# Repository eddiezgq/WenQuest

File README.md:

# 问渠 WenQuest v0.2

问渠 WenQuest：自研前端（网页 + 微信小程序，一套 uni-app 代码）+ 接口网关（FastAPI）+ 开源教学引擎 Moodle 5.2（Claude / DeepSeek 模型接入）。一条命令启动。

v0.3 新增：**AI 建课**。老师描述课程主题、学习对象和章节数（可粘贴自己的大纲或讲义），AI 先出课程大纲，老师修改确认后 AI 逐课撰写内容，预览无误一键发布成真实课程（章节、阅读页、作业），支持中文、英文或中英双语。

v0.2：问渠自己的学习界面和接口网关。学生登录后可看我的课程、课程目录、阅读页、链接、作业说明和文件，中英文一键切换；新界面暂未支持的活动一键跳到经典界面。下一步：带出处的课程 AI 助教。

## 包里有什么

| 内容 | 说明 |
| --- | --- |
| `apps/web/` | 问渠前端（uni-app + Vue 3）：`npm run dev:h5` 本地开发，`npm run build:mp-weixin` 出微信小程序 |
| `services/gateway/` | 接口网关（FastAPI）：登录、课程、内容、文件代理、中英文解析；`python -m pytest` 运行测试 |
| `moodle/setup_wenquest.php` | 启动时开启网关所需的 Web 服务和多语言过滤器 |
| `plugins/local_wenquest/` | 自研 Moodle 插件：一次调用创建整门课程（AI 建课用），并告诉网关当前用户能否建课 |
| `plugins/aiprovider_claude/` | 自研 Moodle 插件：把 Anthropic Claude 接入 Moodle AI 子系统 |
| `moodle/Dockerfile` | Moodle 5.2 镜像（PHP 8.3 + Apache），已内置 Claude 插件和中文语言包 |
| `docker-compose.yml` | Moodle、PostgreSQL 16、Redis、定时任务四个服务 |
| `moodle/setup_ai.php` | 启动时按 `.env` 自动配置 AI 模型、启用 AI 功能、设置中文和时区 |
| `.env.example` | 配置模板 |
| `docker-compose.prod.yml`、`deploy/` | 云服务器生产部署：Caddy 自动 HTTPS、更新、回滚、备份与恢复脚本 |
| `.github/workflows/deploy.yml` | 推送即自动构建镜像并部署到服务器 |
| `site/` | 学院官网（静态页面，中英双语） |
| `factory/` | 问渠数字工厂：ERPNext 减速器厂（`factory/`）与数字工厂第 1 轮（`factory/digital/`：统一数据总线、仿真车间、看板、AI 工厂助手、Node-RED 桥接、FreeCAD 发布）；单独用 Docker 运行，见 `factory/digital/README.md`。只改这里不会触发服务器部署 |
| `docs/上线手册.md` | 从零上线到 DigitalOcean 的分步手册 |

启用后，Moodle 里立即可用的 AI 功能：

- **课程助手**：学生和教师在课程页面一键“总结本页”“解释这段内容”。
- **编辑器 AI**：在任何富文本编辑器里让 AI 起草文字（教案、作业说明、公告等）。

## 上线到云服务器

按 [docs/上线手册.md](docs/上线手册.md) 操作：官网在主域名，问渠学习平台在 `learn.` 子域名，经典界面（Moodle）在 `classic.` 子域名，推送代码即自动部署，每天自动备份。

## 本地快速试用

需要一台 Linux 服务器（建议 4 核 8 GB 内存以上）并安装 Docker 24+。

```bash
cp .env.example .env
nano .env                      # 至少填：MOODLE_WWWROOT、两个密码、一个 AI 密钥
docker compose up -d --build   # 首次构建约 10–20 分钟
docker compose logs -f moodle  # 看到 "Created AI provider" 即完成
```

浏览器打开 `MOODLE_WWWROOT`（经典界面），用 `.env` 里的管理员账号登录、建课、加学生；再打开 `APP_URL`（默认 http://localhost:8088）用学生账号登录问渠新界面。

## AI 建课

- 需要在 `.env` 里填 `ANTHROPIC_API_KEY`（或国内部署填 `DEEPSEEK_API_KEY`），改完执行 `deploy/update.sh`。
- 管理员自动有建课权限。给老师开权限：经典界面 → 网站管理 → 用户 → 权限 → 分配系统角色 → **课程创建者**，把老师加进去。老师重新登录问渠后，“我的课程”右上角会出现 **AI 建课** 按钮。
- AI 生成的内容只是初稿，发布前请老师逐课预览；发布后也可以在经典界面里继续修改。

### 上传资料建课（v0.4）

老师把整个课程资料文件夹拖进来（或点“选择文件夹”），问渠会：

1. 读取 PDF、Word、PPT（含备注）、Excel、文本和图片（单个文件 ≤ 50 MB，一次最多 300 个）；
2. 按文件名、所在文件夹和内容自动分类：教学大纲、教学日历、教案、讲义、课件、作业、测验、参考答案、实验、评分标准、素材；识别每个文件属于第几章，拿不准的标“请确认”，再交给 AI 补判（AI 不会改老师改过的分类）；
3. 老师核对表格后，按资料生成大纲：每章一节，讲义里的小节标题（如 1.1、1.2）变成课，作业文件变成作业，另有“课程说明”“实验”“测验与复习”；
4. AI 撰写每一课时以本章讲义、教案、课件为依据，并注明出处（如“参考：讲义 第 3 页”）；
5. 发布时原始文件作为附件放进对应章节。**教案和参考答案自动设为学生不可见**，只有老师能看到。

扫描版 PDF（图片）暂时读不出文字，会标“无法读取”，仍可作为附件上传。上传的资料只在服务器临时目录保留 24 小时。

## 模型选择

| 场景 | 设置 |
| --- | --- |
| 在美国开发、演示 | 填 `ANTHROPIC_API_KEY`（在 console.anthropic.com 申请；claude.ai 订阅不含 API） |
| 中国大陆部署 | 填 `DEEPSEEK_API_KEY`。DeepSeek 已完成生成式 AI 服务备案，Moodle 5.2 已内置其插件 |
| 两个都填 | 两个模型都启用，在“网站管理 → AI → AI 提供方”里调整优先顺序 |

可选 Claude 模型：`claude-sonnet-5`（默认，质量与速度均衡）、`claude-opus-5-5`（最强，适合复杂批改）、`claude-haiku-4-5-20251001`（最快、成本最低）。
改 `.env` 后执行 `docker compose up -d`，重启时自动更新配置。

## 在中国大陆部署的注意事项

- **合规**：Anthropic 不对中国大陆提供服务；面向国内学校提供生成式 AI 服务须使用已备案模型，并在属地网信办登记。国内部署请只填 `DEEPSEEK_API_KEY`。
- **网络**：Docker Hub 和 GitHub 在国内可能很慢或无法访问。
  - 给 Docker 配置国内镜像加速器（阿里云、腾讯云控制台均提供）。
  - 构建时换成可访问的 Moodle 仓库镜像：
    `docker compose build --build-arg MOODLE_GIT=<镜像地址>`
- **HTTPS**：`docker-compose.prod.yml` 里的 Caddy 会自动申请证书；也可以改用 Nginx 或云负载均衡，并设 `MOODLE_SSLPROXY=true`。

## 只安装插件（已有 Moodle 5.1 及以上）

用 `aiprovider_claude.zip`（GitHub Actions 每次构建都会生成，在该次运行的 Artifacts 里下载）：网站管理 → 插件 → 安装插件 → 上传 zip。
然后在“网站管理 → AI → AI 提供方”新建 Claude 实例并填入 API 密钥，再到“AI 调用位置”启用课程助手和编辑器。

## 日常运维

生产服务器上用 `deploy/` 里的脚本（见上线手册“日常维护”）。本地试用时：

```bash
docker compose ps                                   # 查看状态
docker compose exec db pg_dump -U moodle moodle > backup.sql   # 备份数据库
docker compose up -d --build                        # 更新插件或 Moodle 后重新构建，自动升级数据库
```

`moodledata`（上传的文件）和 `dbdata`（数据库）存放在 Docker 卷中，重建容器不会丢失，但请定期备份。

## 测试情况（v0.1）

- 插件单元测试 23 项全部通过（Moodle 5.2.3，PHP 8.4，PostgreSQL 16）。
- 端到端：通过 Moodle AI 管理器调用生成、摘要、解释三种动作均成功；对真实 Anthropic API 的请求格式和认证已验证（用无效密钥得到预期的 401）。
- 安装流程（生成配置 → 安装数据库 → 配置 AI → 升级）已在全新数据库上验证。
- Docker 镜像本身尚未在服务器上实际构建过，首次构建如有报错请把日志发回。

## 许可

插件与部署脚本以 GNU GPL v3 或更高版本发布，与 Moodle 一致。

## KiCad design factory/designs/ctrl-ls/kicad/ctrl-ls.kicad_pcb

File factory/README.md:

# 问渠虚拟工厂（ERPNext 版）

一座只生产一种产品的虚拟工厂：**二级圆柱齿轮减速器 WQR-105**（传动比 10.5）。装好后，ERPNext 里已经有完整的产品结构、工艺路线、工作中心、质量检验方案、供应商和客户，学生可以直接从销售订单做到发货，走通 MRP、采购、车间报工、质检、序列号追溯和成本核算。

| 文件 | 内容 |
| --- | --- |
| `docker-compose.yml` | ERPNext v16.34.1 单机版（基于官方 frappe_docker），浏览器端口 8090 |
| `seed.py` | 一键导入工厂主数据（可重复运行） |
| `factory/data.py` | 工厂的全部数据：物料、BOM、工艺、工位、检验标准。改工厂就改这个文件 |
| `工厂设计.md` | 工厂设计说明：传动设计、产品结构、成本、瓶颈分析（由 data.py 自动生成） |
| `实验指导.md` | 6 个教学实验：从接单到发货，含不合格品处理和瓶颈改进 |
| `tests/` | 数据一致性检查，以及对照 ERPNext v16 字段定义的模拟导入 |

## 电脑要求

Windows 10/11，内存 16 GB 更流畅（最低 8 GB），磁盘空余 15 GB。ERPNext 会同时运行十来个容器，第一次下载镜像约 2 GB。

## 一、安装 Docker Desktop

从 [docker.com](https://www.docker.com/products/docker-desktop/) 下载 Docker Desktop for Windows，按默认选项安装（使用 WSL 2），装完重启电脑，打开 Docker Desktop 等它显示 “Engine running”。

## 二、启动 ERPNext

本文件夹在问渠仓库的 `factory` 目录里。把仓库克隆到比如 `D:\code\wenquest`（`git clone git@github.com:<你的用户名>/wenquest.git`），在 PowerShell 里：

```powershell
cd D:\code\wenquest\factory
docker compose up -d
docker compose logs -f create-site
```

最后一条命令会显示建站过程，看到它结束（出现 `Current Site set to frontend` 一类的字样后自动退出），按 `Ctrl+C` 离开。首次约 5–10 分钟。

浏览器打开下面这个地址，用户名 `Administrator`，密码 `admin`：

```
http://localhost:8090
```

## 三、完成初始设置向导

第一次登录会进入设置向导，按下面填：

| 项目 | 填写 |
| --- | --- |
| 语言 | English 或 简体中文（两种都可以，导入脚本不受影响） |
| 国家 / 时区 / 币种 | United States / America/New_York / USD |
| 公司名称 | 问渠减速器厂 WenQuest Gearbox（缩写 `WQ`） |
| 会计科目表 | 默认的 Standard |
| 示例数据 | 不要生成（如果向导问到） |

## 四、导入工厂数据

```powershell
py -m pip install -r requirements.txt
py seed.py --opening-stock
```

大约一两分钟。屏幕上会逐项显示进度，最后一行是“完成：新建 N 条”。`--opening-stock` 会放入小五金和齿轮油的期初库存，让实验聚焦在轴承、钢材、铸锻件这些关键物料上。脚本可以重复运行，已存在的记录会跳过。

导入后检查：在 ERPNext 里打开 **BOM** 列表，应有 13 个已提交的 BOM；打开 `WQR-105` 的 BOM，总成本应与《工厂设计.md》末尾的标准成本（约 1,232 美元）接近。

## 五、日常操作

| 要做的事 | 命令 |
| --- | --- |
| 暂停（保留数据） | `docker compose stop` |
| 继续 | `docker compose start` |
| 清空重来（删除全部数据） | `docker compose down -v`，然后重复第二到第四步 |
| 修改工厂设计 | 改 `factory/data.py` → `py -m factory.make_docs` 更新设计文档 → `py seed.py` 导入新增内容 |
| 运行检查 | `py -m pip install pytest`，然后 `py -m pytest tests` |

## 说明

- 默认账号密码都是 `admin`，只适合在自己电脑上学习。要放到服务器给学生用，需要改密码、加 HTTPS，再告诉 Claude 把它并入学习平台的部署。
- `seed.py` 发出的每一条数据都已对照 ERPNext v16 的字段定义做过模拟检查（`tests/test_factory.py`），但还没有在真实的 ERPNext 上运行过。第一次导入如果报错，把屏幕上“出错：”后面的内容发给 Claude。
- 所有供应商、客户都是虚构的示例单位；单价是教学用的示意数值。
- `tests/schemas/` 里的 JSON 文件取自 ERPNext（GPL v3），只用于测试。

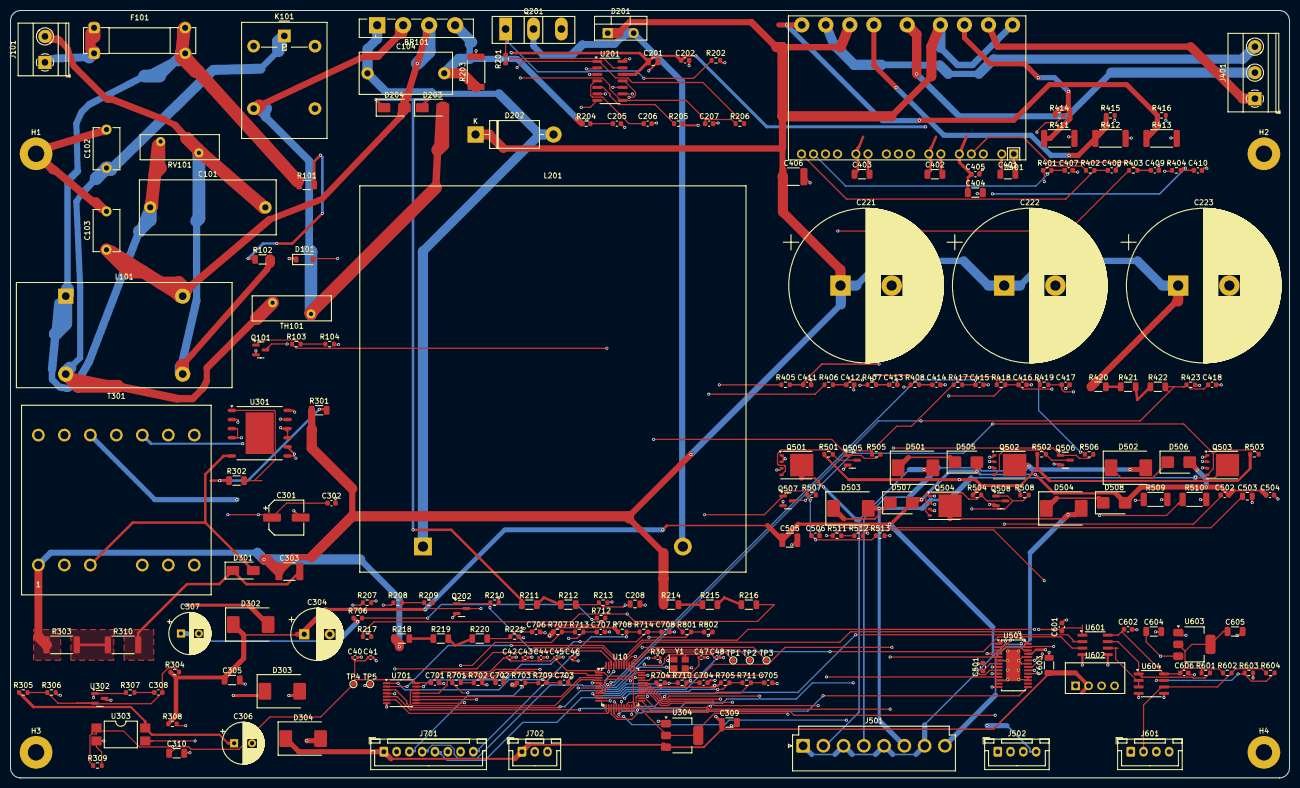
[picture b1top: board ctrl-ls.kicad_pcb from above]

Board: 4 copper layers, 250.0 x 150.0 mm, 226 parts (0 on the bottom side), 150 nets.

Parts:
BR101: GBU1006; Diode_Bridge_Vishay_GBU
C40, C41, C42, C43, C46: 100n; C_0402_1005Metric
C44: 4.7u; C_0402_1005Metric
C45: 1u; C_0402_1005Metric
C47, C48: 10p; C_0402_1005Metric
C101: 470n X2; C_Rect_L26.5mm_W10.5mm_P22.50mm_MKS4
C102, C103: 2n2 Y1; C_Disc_D8.0mm_W5.0mm_P7.50mm
C104: 1u/450V; C_Rect_L18.0mm_W8.0mm_P15.00mm_FKS3_FKP3
C201: 1u/25V; C_0805_2012Metric
C202, C207, C302, C308, C405, C506, C601, C602, C606, C701, C702: 100n; C_0603_1608Metric
C205, C407, C409, C410, C411, C412, C413, C414, C415, C416, C417: 1n; C_0603_1608Metric
C206: 4.7n; C_0603_1608Metric
C208: 3.3u/25V; C_0805_2012Metric
C221, C222, C223: 330u/500V; CP_Radial_D30.0mm_P10.00mm_SnapIn
C301: 47u/16V; CP_Elec_6.3x5.4
C303: 15n/1kV; C_1812_4532Metric
C304: 470u/35V; CP_Radial_D10.0mm_P5.00mm
C305: 1u/50V; C_1206_3216Metric
C306: 220u/25V; CP_Radial_D8.0mm_P3.50mm
C307: 1000u/10V; CP_Radial_D8.0mm_P3.50mm
C309, C310, C404, C604, C605: 10u/25V; C_1206_3216Metric
C401, C402, C403, C603: 4.7u/25V; C_1206_3216Metric
C406: 100n/630V; C_1812_4532Metric
C408, C418: 10n; C_0603_1608Metric
C501: 22n/50V; C_0603_1608Metric
C502, C504: 100n/50V; C_0603_1608Metric
C503: 2.2u; C_0805_2012Metric
C505: 10u/50V; C_1210_3225Metric
C703, C704, C705, C706, C707, C708: 220p; C_0603_1608Metric
D101: 1N4148W; D_SOD-123
D201: C3D06060A; TO-220-2_Vertical
D202: 1N5408; D_DO-201AD_P15.24mm_Horizontal
D203, D204: 1N4007; D_SMA
D301: US1M; D_SMA
D302, D303, D304, D501, D502, D503, D504: ES3D; D_SMC
D505, D506, D507, D508: SMBJ24A; D_SMB
F101: 10A T; Fuseholder_Clip-5x20mm_Bel_FC-203-22_Lateral_P17.80x5.00mm_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
H1, H2, H3, H4: M3; MountingHole_3.2mm_M3_Pad
J101: AC IN L/N; TerminalBlock_Phoenix_MKDS-1,5-2-5.08_1x02_P5.08mm_Horizont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
J401: MOTOR U/V/W; TerminalBlock_Phoenix_MKDS-1,5-3-5.08_1x03_P5.08mm_Horizont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
J501: SOLENOIDS; JST_VH_B8P-VH_1x08_P3.96mm_Vertical
J502: STEPPER; JST_XH_B4B-XH-A_1x04_P2.50mm_Vertical
J601: PANEL; JST_XH_B4B-XH-A_1x04_P2.50mm_Vertical
J701: ENCODER; JST_XH_B8B-XH-A_1x08_P2.50mm_Vertical
J702: PEDAL; JST_XH_B3B-XH-A_1x03_P2.50mm_Vertical
K101: G5LE-1 DC12; Relay_SPDT_Omron-G5LE-1
L101: 7.3mH 9.3A; L_CommonMode_Toroid_Vertical_L41.9mm_W20.3mm_Px15.24mm_Py22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
L201: 451uH; L_ETD59_Horizontal
Q101, Q202, Q505, Q506, Q507, Q508: 2N7002; SOT-23
Q201: IPW60R060P7; TO-247-3_Vertical
Q501, Q502, Q503, Q504: BSC040N08NS5; TDSON-8-1
R30: 10k; R_0402_1005Metric
R101, R102, R420, R421, R422: 1M; R_1206_3216Metric
R103, R308, R309, R402, R414, R415, R416, R709, R710, R711, R712, R713, R714: 1k; R_0603_1608Metric
R104, R210: 100k; R_0603_1608Metric
R201: 3.3; R_0603_1608Metric
R202, R306, R307, R401, R505, R506, R507, R508, R512, R513, R601, R701, R801: 10k; R_0603_1608Metric
R203: 10m; R_2512_6332Metric
R204: 51; R_0603_1608Metric
R205: 66.5k; R_0603_1608Metric
R206, R207, R209: 200k; R_0603_1608Metric
R208: 330k; R_0603_1608Metric
R211, R212: 3.9M; R_1206_3216Metric
R213: 130k; R_0603_1608Metric
R214, R215, R216: 1.02M; R_1206_3216Metric
R217, R221, R702, R802: 20k; R_0603_1608Metric
R218, R219, R220: 1.13M; R_1206_3216Metric
R301, R302: 2M; R_1206_3216Metric
R303, R310: 6.2k; R_2512_6332Metric
R304: 82k; R_0603_1608Metric
R305: 47k; R_0603_1608Metric
R403, R404, R405, R406, R407, R408: 100; R_0603_1608Metric
R411, R412, R413: 25m; R_2512_6332Metric
R417, R418, R419: 15k; R_0603_1608Metric
R423, R511: 22k; R_0603_1608Metric
R501, R502, R503, R504: 4.7k; R_0603_1608Metric
R509, R510: 120m; R_2010_5025Metric
R602, R603: 680; R_0603_1608Metric
R604: 120; R_0603_1608Metric
R703, R704, R705, R706, R707, R708: 2.2k; R_0603_1608Metric
RV101: S14K275; RV_Disc_D15.5mm_W4.9mm_P7.5mm
T301: FLY-24/15/5; Transformer_EPCOS_B66359A1013T_Horizontal
TH101: 2.5R; RV_Disc_D15.5mm_W4.9mm_P7.5mm
TP1: SWDIO; TestPoint_Pad_D1.0mm
TP2: SWCLK; TestPoint_Pad_D1.0mm
TP3: NRST; TestPoint_Pad_D1.0mm
TP4: +3V3; TestPoint_Pad_D1.0mm
TP5: GND; TestPoint_Pad_D1.0mm
U10: STM32G431CBT6; LQFP-48_7x7mm_P0.5mm
U201: ICE3PCS01G; SOIC-14_3.9x8.7mm_P1.27mm
U301: TOP266KG; PowerIntegrations_eSOP-12B
U302: TL431AIDBZR; SOT-23
U303: PC817X2NSZ9F; SMDIP-4_W9.53mm
U304, U603: AMS1117-3.3; SOT-223-3_TabPin2
U401: STGIPS14K60T; ST_SDIP-25L
U501: TMC2226-SA; HTSSOP-28-1EP_4.4x9.7mm_P0.65mm_EP2.75x6.2mm_ThermalVias
U601: ADUM1201ARZ-RL7; SOIC-8_3.9x4.9mm_P1.27mm
U602: B0505S-1WR2; Converter_SIP4_B0505S
U604: MAX3485ESA+T; SOIC-8_3.9x4.9mm_P1.27mm
U701: SN74LVC14APWR; TSSOP-14_4.4x5mm_P0.65mm
Y1: 8MHz; Crystal_SMD_3225-4Pin_3.2x2.5mm

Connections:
+3V3: C40.1, C41.1, C42.1, C43.1, C44.1, C45.1, C310.1, C506.1, C601.1, C701.1, R401.1, R402.1, R417.1, R418.1, R419.1, R505.1, R506.1, R507.1, R508.1, R513.1, TP4.1, U10.1, U10.20, U10.21, U10.24, U10.36, U10.48, U304.2, U501.19, U601.1, U701.14
+3V3_ISO: C602.1, C605.1, C606.1, R601.1, R602.1, U601.8, U603.2, U604.8
+5V: C307.1, C309.1, C603.1, D304.1, J701.1, J702.1, R703.1, R704.1, R705.1, R706.1, R707.1, R708.1, U304.3, U602.2
+5V_ISO: C604.1, J601.1, U602.4, U603.3
+15V: C201.1, C202.1, C306.1, C404.1, C405.1, D101.1, D303.1, K101.2, R305.1, R501.1, R502.1, R503.1, R504.1, U201.12, U303.4, U401.5
+24V: C304.1, C305.1, C502.2, C504.1, C505.1, D302.1, D505.2, D506.2, D507.2, D508.2, J501.1, J501.3, J501.5, J501.7, R304.1, R308.1, U501.3, U501.26
BOFO: R206.2, R207.1, U201.1
BOOT0: R30.1, U10.45
BOP: C208.1, R212.2, R213.1, U201.9
BRO_A: D203.1, D204.1, R211.1
BRO_B: R211.2, R212.1
CLAMP: C303.2, D301.1, R310.2
CLAMP_M: R303.2, R310.1
ENC_A: J701.3, R703.2, R709.1
ENC_A_F: U10.43, U701.2
ENC_A_RC: C703.1, R709.2, U701.1
ENC_B: J701.4, R704.2, R710.1
ENC_B_F: U10.44, U701.4
ENC_B_RC: C704.1, R710.2, U701.3
ENC_Z: J701.5, R705.2, R711.1
ENC_Z_F: U10.14, U701.6
ENC_Z_RC: C705.1, R711.2, U701.5
FB_K: R307.1, R309.2, U302.1, U303.2
FB_LED: R308.2, R309.1, U303.1
FB_RC: C308.1, R307.2
FB_REF: C308.2, R304.2, R305.2, R306.1, U302.2
FLY_5: D304.2, T301.12
FLY_15: D303.2, T301.10
FLY_24: D302.2, T301.8
FLY_D: D301.2, T301.3, U301.6
FREQ: R205.1, U201.5
GATE_IC: R201.1, U201.13
GATE_PFC: Q201.1, R201.2, R202.1
GND: C40.2, C41.2, C42.2, C43.2, C44.2, C45.2, C46.2, C47.2, C48.2, C201.2, C202.2, C205.2, C206.2, C207.2, C208.2, C221.2, C222.2, C223.2, C301.2, C302.2, C304.2, C305.2, C306.2, C307.2, C309.2, C310.2, C404.2, C405.2, C406.2, C407.2, C408.2, C409.2, C410.2, C411.2, C412.2, C413.2, C414.2, C415.2, C416.2, C417.2, C418.2, C503.2, C504.2, C505.2, C506.2, C601.2, C603.2, C701.2, C702.2, C703.2, C704.2, C705.2, C706.2, C707.2, C708.2, J701.2, J702.3, Q101.2, Q201.3, Q202.2, Q501.1, Q501.2, Q501.3, Q502.1, Q502.2, Q502.3, Q503.1, Q503.2, Q503.3, Q504.1, Q504.2, Q504.3, Q505.2, Q506.2, Q507.2, Q508.2, R30.2, R104.2, R202.2, R203.2, R205.2, R207.2, R209.2, R210.2, R213.2, R217.2, R221.2, R306.2, R411.2, R412.2, R413.2, R423.2, R509.2, R510.2, R512.2, R702.2, R802.2, T301.9, T301.11, T301.13, TP5.1, U10.19, U10.23, U10.35, U10.47, U201.3, U201.14, U301.2, U301.7, U301.8, U301.9, U301.10, U301.11, U301.12, U302.3, U304.1, U401.8, U501.6, U501.10, U501.12, U501.14, U501.17, U501.18, U501.22, U501.24, U501.29, U601.4, U602.1, U701.7, Y1.2, Y1.4
GND_ISO: C602.2, C604.2, C605.2, C606.2, J601.4, R603.2, U601.5, U602.3, U603.1, U604.4, U604.5
HALL_U: J701.6, R706.2, R712.1
HALL_U_F: U10.2, U701.8
HALL_U_RC: C706.1, R712.2, U701.9
HALL_V: J701.7, R707.2, R713.1
HALL_V_F: U10.3, U701.10
HALL_V_RC: C707.1, R713.2, U701.11
HALL_W: J701.8, R708.2, R714.1
HALL_W_F: U10.4, U701.12
HALL_W_RC: C708.1, R714.2, U701.13
ICOMP: C206.1, U201.4
IN_UH: C409.1, R403.2, U401.4
IN_UL: C410.1, R404.2, U401.3
IN_VH: C411.1, R405.2, U401.10
IN_VL: C412.1, R406.2, U401.9
IN_WH: C413.1, R407.2, U401.14
IN_WL: C414.1, R408.2, U401.13
IPM_SD: C407.1, R401.2, U10.26, U401.15
IPM_T: C408.1, R402.2, U10.12, U401.16
ISENSE: C205.1, R204.2, U201.2
ISNS_U: C415.1, R414.2, R417.2, U10.9
ISNS_V: C416.1, R415.2, R418.2, U10.15
ISNS_W: C417.1, R416.2, R419.2, U10.16
L_C: C102.1, K101.1, L101.2, TH101.1
L_F: C101.1, F101.2, L101.1, R101.1, RV101.1
L_IN: F101.1, J101.1
L_R: BR101.2, D203.2, K101.3, TH101.2
MOT_U: J401.1, U401.24
MOT_V: J401.2, U401.21
MOT_W: J401.3, U401.18
NRST: C46.1, TP3.1, U10.7
N_C: BR101.3, C103.1, D204.2, L101.4
N_IN: C101.2, J101.2, L101.3, R102.2, RV101.2
N_U: R411.1, R414.1, U401.23
N_V: R412.1, R415.1, U401.20
N_W: R413.1, R416.1, U401.17
OSC_IN: C47.1, U10.5, Y1.1
OSC_OUT: C48.1, U10.6, Y1.3
OUT_U: C401.2, U401.1
OUT_V: C402.2, U401.6
OUT_W: C403.2, U401.11
OVP: R220.2, R221.1, U201.10
OVP_1: R218.2, R219.1
OVP_2: R219.2, R220.1
PE: C102.2, C103.2, H1.1
PEDAL: C702.1, R701.2, R702.1, U10.17
PEDAL_IN: J702.2, R701.1
PFC_OFF: Q202.1, R210.1, U10.46
PNL_A: J601.2, R602.2, R604.1, U604.6
PNL_B: J601.3, R603.1, R604.2, U604.7
PNL_RX: U10.11, U601.2
PNL_TX: U10.10, U601.3
PWM_UH: R403.1, U10.30
PWM_UL: R404.1, U10.27
PWM_VH: R405.1, U10.31
PWM_VL: R406.1, U10.28
PWM_WH: R407.1, U10.32
PWM_WL: R408.1, U10.29
RECT_N: BR101.4, C104.2, R203.1, R204.1
RLY_G: Q101.1, R103.2, R104.1
RLY_K: D101.2, K101.5, Q101.3
RO_ISO: R601.2, U601.7, U604.1
SOL1_D: D501.2, J501.2, Q501.5
SOL1_G: Q501.4, Q505.3, R501.2
SOL1_K: D501.1, D505.1
SOL2_D: D502.2, J501.4, Q502.5
SOL2_G: Q502.4, Q506.3, R502.2
SOL2_K: D502.1, D506.1
SOL3_D: D503.2, J501.6, Q503.5
SOL3_G: Q503.4, Q507.3, R503.2
SOL3_K: D503.1, D507.1
SOL4_D: D504.2, J501.8, Q504.5
SOL4_G: Q504.4, Q508.3, R504.2
SOL4_K: D504.1, D508.1
SOL_FOOT: Q508.1, R508.2, U10.39
SOL_REV: Q507.1, R507.2, U10.34
SOL_TRIM: Q505.1, R505.2, U10.13
SOL_WIPE: Q506.1, R506.2, U10.33
STP_5V: C503.1, R511.1, U501.11
STP_BRA: R509.1, U501.27
STP_BRB: R510.1, U501.2
STP_CPI: C501.2, U501.8
STP_CPO: C501.1, U501.7
STP_DIAG: U10.18, U501.15
STP_DIR: U10.42, U501.23
STP_EN: R513.2, U10.25, U501.5
STP_OA1: J502.1, U501.28
STP_OA2: J502.2, U501.25
STP_OB1: J502.3, U501.1
STP_OB2: J502.4, U501.4
STP_STEP: U10.41, U501.20
STP_VCP: C502.1, U501.9
STP_VREF: R511.2, R512.1, U501.21
SWCLK: TP2.1, U10.38
SWDIO: TP1.1, U10.37
SW_PFC: D201.2, L201.2, Q201.2
TOP_C: C301.1, C302.1, U301.3, U301.4, U303.3
TOP_V: R302.2, U301.1
TOP_V1: R301.2, R302.1
TXN_ISO: U601.6, U604.2, U604.3
VBTHL_EN: Q202.3, R208.2, R209.1, U201.7
VBUS: C221.1, C222.1, C223.1, C303.1, C406.1, D201.1, D202.1, R214.1, R218.1, R301.1, R303.1, R420.1, T301.1, U401.19, U401.22, U401.25
VBUS_SNS: C418.1, R422.2, R423.1, U10.8
VBUS_SNS_1: R420.2, R421.1
VBUS_SNS_2: R421.2, R422.1
VB_OK: R103.1, R801.1, U201.6
VB_OK_SNS: R801.2, R802.1, U10.40
VB_U: C401.1, U401.2
VB_V: C402.1, U401.7
VB_W: C403.1, U401.12
VRECT: BR101.1, C104.1, D202.2, L201.1
VREF: C207.1, R206.1, R208.1, U201.8
VSENSE: R216.2, R217.1, U201.11
VSENSE_1: R214.2, R215.1
VSENSE_2: R215.2, R216.1
XDIS: R101.2, R102.1

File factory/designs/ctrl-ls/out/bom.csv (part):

物料编号,数值,封装,数量,位号,型号,厂家,立创编号,说明
BRG-GBU1006,GBU1006,Diode_Bridge_Vishay_GBU,1,BR101,GBU1006,LGE,C5183365,整流桥（符号和封装用 KiCad 官方库的 GBU 系列：1 +、2 ~、3 ~、4 −；装在散热器上）
CAP-0402,100n,C_0402_1005Metric,5,C40 C41 C42 C43 C46,,,,
CAP-0402,10p,C_0402_1005Metric,2,C47 C48,,,,
CAP-0402,1u,C_0402_1005Metric,1,C45,,,,VDDA
CAP-0402,4.7u,C_0402_1005Metric,1,C44,,,,
CAP-0603,100n,C_0603_1608Metric,11,C202 C207 C302 C308 C405 C506 C601 C602 C606 C701 C702,,,,
CAP-0603,100n/50V,C_0603_1608Metric,2,C502 C504,,,,
CAP-0603,10n,C_0603_1608Metric,2,C408 C418,,,,
CAP-0603,1n,C_0603_1608Metric,11,C205 C407 C409 C410 C411 C412 C413 C414 C415 C416 C417,,,,规格书 p.7 物料表 CISENSE 1 nF
CAP-0603,220p,C_0603_1608Metric,6,C703 C704 C705 C706 C707 C708,,,,
CAP-0603,22n/50V,C_0603_1608Metric,1,C501,,,,电荷泵（BOB 物料清单）
CAP-0603,4.7n,C_0603_1608Metric,1,C206,,,,电流环补偿（规格书 p.7 物料表 CICOMP 4.7 nF）
CAP-0805,1u/25V,C_0805_2012Metric,1,C201,,,,VCC 去耦（规格书没给值，设计取值）
CAP-0805,2.2u,C_0805_2012Metric,1,C503,,,,片内 5 V 稳压输出
CAP-0805,3.3u/25V,C_0805_2012Metric,1,C208,,,,规格书 p.7 CBRO 3 µF，取 3.3 µF
CAP-1206,10u/25V,C_1206_3216Metric,5,C309 C310 C404 C604 C605,,,,
CAP-1206,1u/50V,C_1206_3216Metric,1,C305,,,,
CAP-1206,4.7u/25V,C_1206_3216Metric,4,C401 C402 C403 C603,,,,自举电容：静态电流 300 µA（规格书）× 每个 PWM 周期 62.5 µs ≪ 4.7 µF × 1 V
CAP-1210,10u/50V,C_1210_3225Metric,1,C505,,,,VS 去耦
CAP-1812-1KV,15n/1kV,C_1812_4532Metric,1,C303,,,,RCD 钳位电容（计算书：≥ 11.6n）
CAP-1812-630V,100n/630V,C_1812_4532Metric,1,C406,,,,母线高频旁路，紧靠 P、N 引脚（规格书 4.1 节）
CAP-BULK-330U-500V,330u/500V,CP_Radial_D30.0mm_P10.00mm_SnapIn,3,C221 C222 C223,500MXH330MEFCSN30X50,Rubycon,C472902,500MXH330MEFCSN30X50（母线电容，计算书：3 只并联）
CAP-EL-1000U-10V,1000u/10V,CP_Radial_D8.0mm_P3.50mm,1,C307,,,,5 V 输出
CAP-EL-220U-25V,220u/25V,CP_Radial_D8.0mm_P3.50mm,1,C306,,,,15 V 输出（功率模块、校正控制器、继电器）
CAP-EL-470U-35V,470u/35V,CP_Radial_D10.0mm_P5.00mm,1,C304,,,,24 V 输出（电磁铁吸合的脉冲电流从这里出）
CAP-EL-47U-16V,47u/16V,CP_Elec_6.3x5.4,1,C301,,,,C 脚旁路 47 µF（规格书 p.8：起动 / 重启时间按 47 µF 给出）
CAP-FILM-1U-450V,1u/450V,C_Rect_L18.0mm_W8.0mm_P15.00mm_FKS3_FKP3,1,C104,,,,整流后高频旁路（吸收升压管开关电流，薄膜电容）
CAP-X2-470N,470n X2,C_Rect_L26.5mm_W10.5mm_P22.50mm_MKS4,1,C101,BFC233920474,Vishay,C511073,BFC233920474（封装待核对）
CAP-Y-2N2,2n2 Y1,C_Disc_D8.0mm_W5.0mm_P7.50mm,2,C102 C103,DE1E3RA222MA4BP01F,Murata,C907949,Y 电容（封装待核对）
CMC-8118RC,7.3mH 9.3A,L_CommonMode_Toroid_Vertical_L41.9mm_W20.3mm_Px15.24mm_Py22.86mm_Bourns_8100,1,L101,8118-RC,Bourns,,8118-RC（Bourns 8100 系列，KiCad 官方库同系列封装；159d2 由 FC-HLF2018 换来：那颗规格书读不出、库里没有封装）
CONN-AC,AC IN L/N/PE,"TerminalBlock_Phoenix_MKDS-1,5-3-5.08_1x03_P5.08mm_Horizontal",1,J101,,,,交流输入：1 相线、2 零线、3 保护地
CONN-MOT,MOTOR U/V/W,"TerminalBlock_Phoenix_MKDS-1,5-3-5.08_1x03_P5.08mm_Horizontal",1,J401,,,,电机三相
CONN-VH8,SOLENOIDS,JST_VH_B8P-VH_1x08_P3.96mm_Vertical,1,J501,,,,电磁铁 4 路（每路 +24 V 与漏极）：剪线、拨线、倒缝、抬压脚
CONN-XH3,PEDAL,JST_XH_B3B-XH-A_1x03_P2.50mm_Vertical,1,J702,,,,脚踏板（霍尔，0.5–4.5 V）
CONN-XH4,PANEL,JST_XH_B4B-XH-A_1x04_P2.50mm_Vertical,1,J601,,,,操作面板（隔离侧，人能碰到的唯一接口）
CONN-XH4,STEPPER,JST_XH_B4B-XH-A_1x04_P2.50mm_Vertical,1,J502,,,,针距步进电机
CONN-XH8,ENCODER,JST_XH_B8B-XH-A_1x08_P2.50mm_Vertical,1,J701,,,,电机编码器与霍尔
DCDC-B0505S,B0505S-1WR2,Converter_SIP4_B0505S,1,U602,B0505S-1WR2,YLPTEC,C2992393,隔离电源 5 V → 5 V 1 W，隔离 1500 V 直流 1 分钟（Mornsun 原版规格书）。规格书写“行业标准引脚”、图读不出：按 1 W 单列直插行业通用排法 1 −Vin、2 +Vin、3 −Vo、4 +Vo、间距 2.54 mm 做封装，待核对
DIO-1N4007,1N4007,D_SMA,2,D203 D204,,,,欠压取样（规格书 p.7 DBRO1、DBRO2；贴片 M7 等效）
DIO-1N4148W,1N4148W,D_SOD-123,1,D101,,,,继电器线圈续流
DIO-1N5408,1N5408,D_DO-201AD_P15.24mm_Horizontal,1,D202,,,,旁路二极管：上电时浪涌电流绕过电感直接给母线电容充电（规格书 p.7 物料表 DBYP 的作用，型号是设计取值）
DIO-C3D06060A,C3D06060A,TO-220-2_Vertical,1,D201,C3D06060A,Wolfspeed (Cree),C5693025,升压二极管（碳化硅；符号和封装用 KiCad 官方库的 C3D06060A：1 阴极、2 阳极；装在散热器上）
DIO-ES3D,ES3D,D_SMC,7,D302 D303 D304 D501 D502 D503 D504,ES3D,onsemi,C241735,24 V 整流
DIO-US1M,US1M,D_SMA,1,D301,,,,钳位二极管（快恢复 1000 V）
FUSE-T10A,10A T,Fuseholder_Clip-5x20mm_Bel_FC-203-22_Lateral_P17.80x5.00mm_D1.17mm_Horizontal,1,F101,0215010.MXP,Littelfuse,C142733,0215010.MXP（5×20 mm 慢断，夹座安装；夹座封装待核对）
IC-74LVC14,SN74LVC14APWR,TSSOP-14_4.4x5mm_P0.65mm,1,U701,SN74LVC14APWR,Texas Instruments,C7663,施密特整形（六路）
IC-ADUM1201,ADUM1201ARZ-RL7,SOIC-8_3.9x4.9mm_P1.27mm,1,U601,ADUM1201ARZ-RL7,Analog Devices,C9669,数字隔离：B 通道主控 → 面板（发送），A 通道面板 → 主控（接收）
IC-LDO-3V3,AMS1117-3.3,SOT-223-3_TabPin2,2,U304 U603,,,,3.3 V（沿用关节驱动板）
IC-MCU-MC,STM32G431CBT6,LQFP-48_7x7mm_P0.5mm,1,U10,STM32G431CBT6,STMicroelectronics,C529355,主控（沿用关节驱动板）：TIM1 三相互补 PWM、片内运放采三相电流、ADC 测母线与模块温度、TIM4 编码器、USART2 面板口、TIM3 步进脉冲
IC-PFC-ICE3PCS01G,ICE3PCS01G,SOIC-14_3.9x8.7mm_P1.27mm,1,U201,ICE3PCS01G,Infineon,C192050,连续导通功率因数校正控制器
IC-RS485,MAX3485ESA+T,SOIC-8_3.9x4.9mm_P1.27mm,1,U604,MAX3485ESA+T,Analog Devices (Maxim),C18148,RS-485 收发（DE、/RE 由发送信号控制，DI 接地）
IC-TL431,TL431AIDBZR,SOT-23,1,U302,TL431AIDBZR,Texas Instruments,C23892,反馈基准
IC-TMC2226,TMC2226-SA,HTSSOP-28-1EP_4.4x9.7mm_P0.65mm_EP2.75x6.2mm_ThermalVias,1,U501,TMC2226-SA,ADI / Trinamic,C6718351,针距步进驱动：MS1、MS2 接地（8 细分）、SPREAD 接地（静音模式）、CLK 接地（片内时钟）、PDN_UART 接地（停转时电流减半）、STDBY 接地；以上独立模式接法待核对规格书
IC-TOP266KG,TOP266KG,PowerIntegrations_eSOP-12B,1,U301,TOP266KG,Power Integrations,C568204,反激控制器（集成 725 V 开关管）；X 接 S、F 接 C
IND-PFC-CUSTOM,451uH,L_ETD59_Horizontal,1,L201,,,,升压电感（定制：ETD59 + 骨架 B66398，匝数、气隙、线径见计算书“按理论”）
IPM-STGIPS14K60T,STGIPS14K60T,ST_SDIP-25L,1,U401,STGIPS14K60T,STMicroelectronics,C5268145,三相智能功率模块（装在散热器上）。OUT_x 是上桥浮地参考，自举电容接在 VB_x 与 OUT_x 之间
MOS-2N7002,2N7002,SOT-23,6,Q101 Q202 Q505 Q506 Q507 Q508,,,,母线充好（校正控制器 VB_OK = 5 V）后吸合
MOS-80V,BSC040N08NS5,TDSON-8-1,4,Q501 Q502 Q503 Q504,BSC040N08NS5,Infineon,C534333,剪线电磁铁
MOS-IPW60R060P7,IPW60R060P7,TO-247-3_Vertical,1,Q201,IPW60R060P7,Infineon,C454258,升压开关管（TO-247：1 G、2 D、3 S；装在散热器上）
MOV-275,S14K275,RV_Disc_D15.5mm_W4.9mm_P7.5mm,1,RV101,B72214S0271K101,TDK,C7502584,B72214S0271K101（封装按 14 mm 盘片选，待核对）
NTC-2R5,2.5R,RV_Disc_D15.5mm_W4.9mm_P7.5mm,1,TH101,B57364S0259M000,TDK,C17362791,B57364S0259M000（上电浪涌限流，母线充好后由 K101 短接；封装按盘片选，待核对）
OPTO-PC817,PC817X2NSZ9F,SMDIP-4_W9.53mm,1,U303,PC817X2NSZ9F,Sharp,C390734,反馈光耦（这里不为隔离，只为把误差电流送进 C 脚）
RES-0402,10k,R_0402_1005Metric,1,R30,,,,BOOT0 下拉
RES-0603,100,R_0603_1608Metric,6,R403 R404 R405 R406 R407 R408,,,,输入 RC 滤波 100 Ω / 1 nF（0.1 µs ≪ 死区 1 µs，设计取值）
RES-0603,100k,R_0603_1608Metric,2,R104 R210,,,,
RES-0603,10k,R_0603_1608Metric,13,R202 R306 R307 R401 R505 R506 R507 R508 R512 R513 R601 R701 R801,,,,栅源下拉（设计取值）
RES-0603,120,R_0603_1608Metric,1,R604,,,,终端电阻（控制器在总线一端）
RES-0603,130k,R_0603_1608Metric,1,R213,,,,规格书 p.7 RBRO3 130 kΩ
RES-0603,15k,R_0603_1608Metric,3,R417 R418 R419,,,,
RES-0603,1k,R_0603_1608Metric,13,R103 R308 R309 R402 R414 R415 R416 R709 R710 R711 R712 R713 R714,,,,VB_OK 最多出 1 mA（ICE3PCS01G 规格书 p.19），只推管子栅极
RES-0603,2.2k,R_0603_1608Metric,6,R703 R704 R705 R706 R707 R708,,,,上拉到 5 V
RES-0603,200k,R_0603_1608Metric,3,R206 R207 R209,,,,BOFO 拉到 0.5 V 以上 = 不用升压跟随（规格书 p.13）；200 k / 200 k 照 p.7 物料表
RES-0603,20k,R_0603_1608Metric,4,R217 R221 R702 R802,,,,VSENSE 下臂
RES-0603,22k,R_0603_1608Metric,2,R423 R511,,,,
RES-0603,3.3,R_0603_1608Metric,1,R201,,,,栅极电阻 3.3 Ω（规格书 p.7 物料表 RGATE）
RES-0603,330k,R_0603_1608Metric,1,R208,,,,VB_OK 断开门限 = 5 V × 200/530 = 1.89 V（母线约 294 V）；330 k / 200 k 照 p.7 物料表 RVB1、RVB2，接法是按框图读的，待核对
RES-0603,4.7k,R_0603_1608Metric,4,R501 R502 R503 R504,,,,栅极上拉到 15 V
RES-0603,47k,R_0603_1608Metric,1,R305,,,,
RES-0603,51,R_0603_1608Metric,1,R204,,,,ISENSE 串联电阻约 50 Ω，限浪涌（规格书 p.4、p.7 物料表 RCS）
RES-0603,66.5k,R_0603_1608Metric,1,R205,,,,开关频率：规格书 67 kΩ → 65 kHz（p.7–8），取 E96 最近的 66.5 kΩ
RES-0603,680,R_0603_1608Metric,2,R602 R603,,,,总线空闲偏置（A 上拉、B 下拉）
RES-0603,82k,R_0603_1608Metric,1,R304,,,,加权取样：24 V 与 15 V 各占一半（设计取值），下臂 10 k
RES-1206,1.02M,R_1206_3216Metric,3,R214 R215 R216,,,,VSENSE 上臂 3 × 1.02M（理想 3.1 MΩ）：母线 = 2.5 V × (1 + 上/下)
RES-1206,1.13M,R_1206_3216Metric,3,R218 R219 R220,,,,OVP 上臂 3 × 1.13M：第二级过压约 110 % 额定（429 V，设计取值）
RES-1206,1M,R_1206_3216Metric,5,R101 R102 R420 R421 R422,,,,X 电容放电：2 MΩ × 0.47 µF = 0.94 s（拔插头后 1 s 内放到安全）
RES-1206,2M,R_1206_3216Metric,2,R301 R302,,,,V 脚线路检测 4 MΩ（规格书 p.6），两只 1206 串联分压；离 V 脚 10 mm 内（p.21）
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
